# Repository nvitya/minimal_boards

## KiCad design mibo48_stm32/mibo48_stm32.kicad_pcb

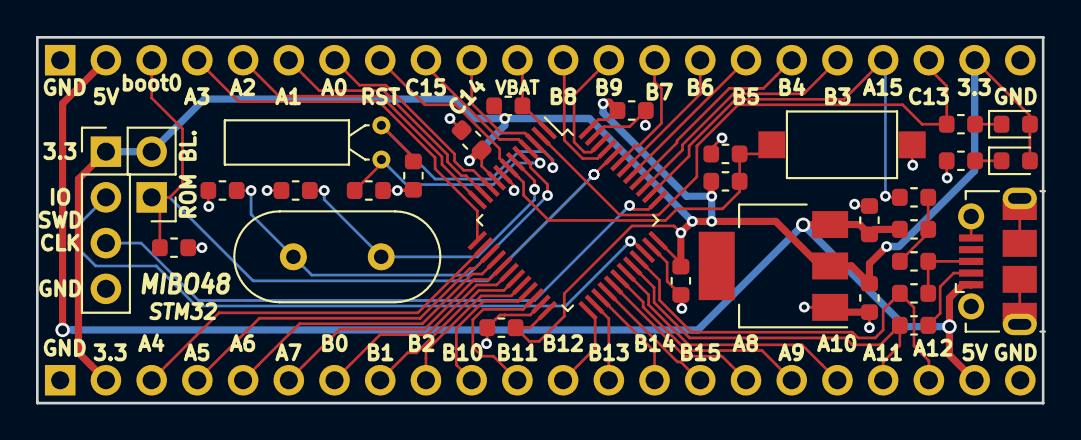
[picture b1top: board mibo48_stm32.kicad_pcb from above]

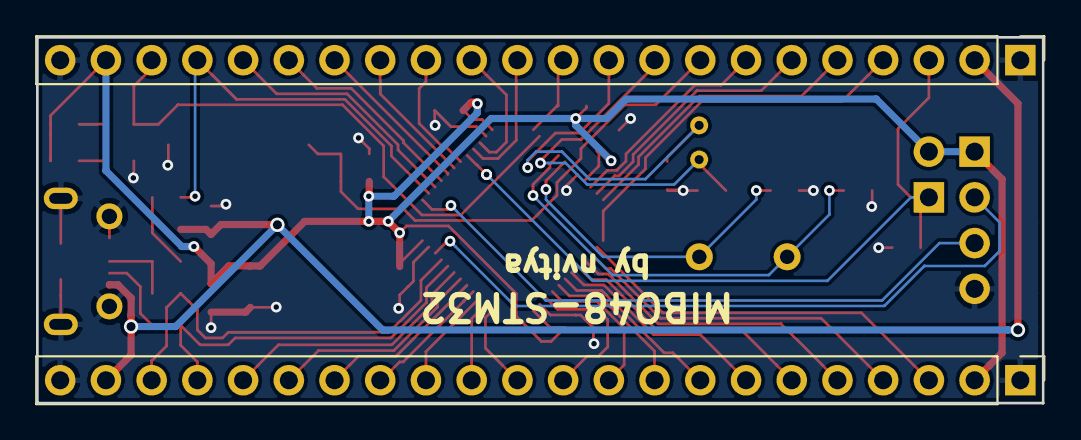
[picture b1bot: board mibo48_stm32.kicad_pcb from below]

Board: 2 copper layers, 55.9 x 20.3 mm, 33 parts (2 on the bottom side), 48 nets.

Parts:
C1, C2, C9, C10: 22pF; C_0603_1608Metric
C3: 10nF; C_0603_1608Metric
C4, C5, C6, C7: 100nF; C_0603_1608Metric
C8, C11: 4.7uF; C_0603_1608Metric
D1, D2: GREEN; LED_0603_1608Metric
J1: Conn_01x02; PinHeader_1x02_P2.54mm_Vertical
J2, J3: Conn_01x22; PinHeader_1x22_P2.54mm_Vertical
J4: USB_B_Micro; USB_Micro-B_Molex-105017-0001
J5: Conn_01x04; PinHeader_1x04_P2.54mm_Vertical
R1: 100k; R_0603_1608Metric
R2: 10k; R_0603_1608Metric
R3, R10: 1k; R_0603_1608Metric
R4, R5, R6: 0R; R_0603_1608Metric
R7: 1.5k; R_0603_1608Metric
R8, R9: 22R; R_0603_1608Metric
SW1: Reset; SW_SPST_CK_RS282G05A3
U1: STM32F303CBTx; LQFP-48_7x7mm_P0.5mm
U2: AMS1117-3.3; SOT-223
Y1: 8MHz; Crystal_HC49-4H_Vertical
Y2: 32.768kHz; Crystal_C26-LF_D2.1mm_L6.5mm_Horizontal

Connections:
+3V3: C4.1, C5.1, C6.1, C7.1, C11.1, D1.2, D2.2, J1.2, J2.2, J3.21, J5.1, R2.2, R4.2, U1.9, U1.24, U1.36, U1.48, U2.2
/5V: C8.1, J2.21, J3.2, J4.1, R6.1, U2.3
/BOOT0: J1.1, J3.3, R1.1, U1.44
/LED1: J3.20, R3.1, U1.2
/OSC32_IN: C9.1, J3.10, U1.3, Y2.1
/OSC32_OUT: C10.1, J3.9, U1.4, Y2.2
/OSC_IN: C1.1, U1.5, Y1.1
/OSC_OUT: C2.1, U1.6, Y1.2
/PA0: J3.7, U1.10
/PA1: J3.6, U1.11
/PA2: J3.5, U1.12
/PA3: J3.4, U1.13
/PA4: J2.3, U1.14
/PA5: J2.4, U1.15
/PA6: J2.5, U1.16
/PA7: J2.6, U1.17
/PA8: J2.16, U1.29
/PA9: J2.17, U1.30
/PA10: J2.18, U1.31
/PA11: J2.19, R9.1, U1.32
/PA12: J2.20, R8.1, U1.33
/PA15: J3.19, R5.2, U1.38
/PB0: J2.7, U1.18
/PB1: J2.8, U1.19
/PB2: J2.9, U1.20
/PB3: J3.18, U1.39
/PB4: J3.17, U1.40
/PB5: J3.16, U1.41
/PB6: J3.15, U1.42
/PB7: J3.14, U1.43
/PB8: J3.12, U1.45
/PB9: J3.13, U1.46
/PB10: J2.10, U1.21
/PB11: J2.11, U1.22
/PB12: J2.12, U1.25
/PB13: J2.13, U1.26
/PB14: J2.14, U1.27
/PB15: J2.15, U1.28
/RESET: C3.1, J3.8, R2.1, SW1.1, U1.7
/SWDCLK: J5.3, U1.37
/SWDIO: J5.2, U1.34
/VBAT: J3.11, R4.1, U1.1
GND: C1.2, C2.2, C3.2, C4.2, C5.2, C6.2, C7.2, C8.2, C9.2, C10.2, C11.2, J2.1, J2.22, J3.1, J3.22, J4.5, J4.6, J5.4, R1.2, R10.1, SW1.2, U1.8, U1.23, U1.35, U1.47, U2.1
unnamed: D1.1, R3.2
unnamed: D2.1, R10.2
unnamed: J4.2, R9.2
unnamed: J4.3, R7.1, R8.2
unnamed: R5.1, R6.2, R7.2
